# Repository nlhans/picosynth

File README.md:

# picosynth
Raspberry Pi Pico hat for synthesizer stack, USB host and MIDI input

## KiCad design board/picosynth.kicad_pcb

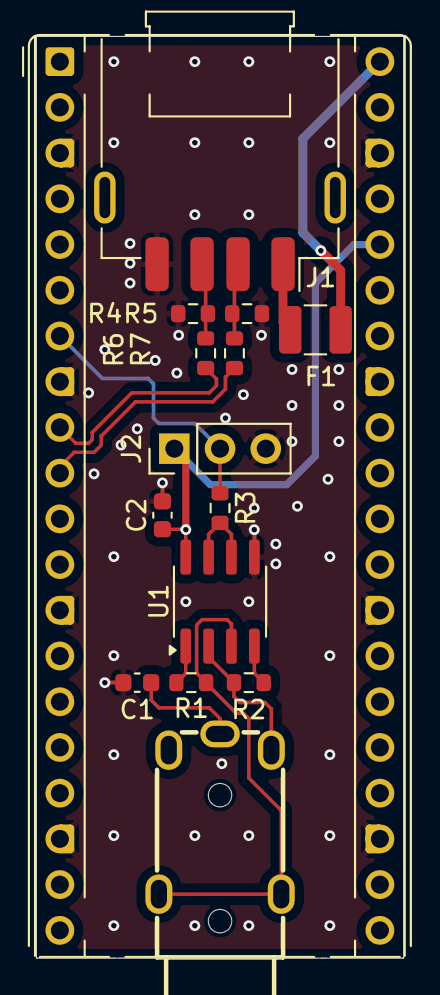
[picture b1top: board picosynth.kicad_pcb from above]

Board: 2 copper layers, 20.4 x 51.2 mm, 15 parts (0 on the bottom side), 15 nets.

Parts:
A1: RaspberryPi_Pico; RaspberryPi_Pico_Common_THT
C1, C2: 100nF; C_0603_1608Metric
CN1: PJ-3220-Y; AUDIO-TH_PJ-3220-Y
F1: Yageo SMD1210B075TF; Fuse_1210_3225Metric
J1: USB_A; USB_A_Receptacle_GCT_USB1046
J2: Conn_01x03; PinHeader_1x03_P2.54mm_Vertical
R1, R2: 220R; R_0603_1608Metric
R3: 1k; R_0603_1608Metric
R4, R5: 15k; R_0603_1608Metric
R6, R7: 22R; R_0603_1608Metric
U1: HCPL-0631-500E; SOIC-8_3.9x4.9mm_P1.27mm

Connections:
+3.3V: A1.36 (3V3), C2.1, J2.1, U1.8 (VCC)
+5V: A1.40 (VBUS), F1.2
/MIDI_IN: A1.7 (GPIO5), J2.2, R3.1
/USBH_D+: A1.9 (GPIO6), R6.2
/USBH_D-: A1.10 (GPIO7), R7.2
/_MIDIIN1: CN1.4, R2.1, U1.2 (C1)
/_MIDIIN2: CN1.3, R1.1, U1.3 (C2)
GND: A1.3 (GND), A1.8 (GND), A1.13 (GND), A1.18 (GND), A1.23 (GND), A1.28 (GND), A1.38 (GND), C1.1, C2.2, J1.4 (GND), J2.3, R4.2, R5.2, U1.5 (GND)
unnamed: C1.2, CN1.1
unnamed: J1.3 (D+), R4.1, R6.1
unnamed: J1.2 (D-), R5.1, R7.1
unnamed: F1.1, J1.1 (VBUS)
unnamed: R1.2, U1.1 (A1)
unnamed: R2.2, U1.4 (A2)
unnamed: R3.2, U1.6 (VO2), U1.7 (VO1)

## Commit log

2026-05-29 Initial design
2026-05-29 Exports
2026-05-29 DS Store
